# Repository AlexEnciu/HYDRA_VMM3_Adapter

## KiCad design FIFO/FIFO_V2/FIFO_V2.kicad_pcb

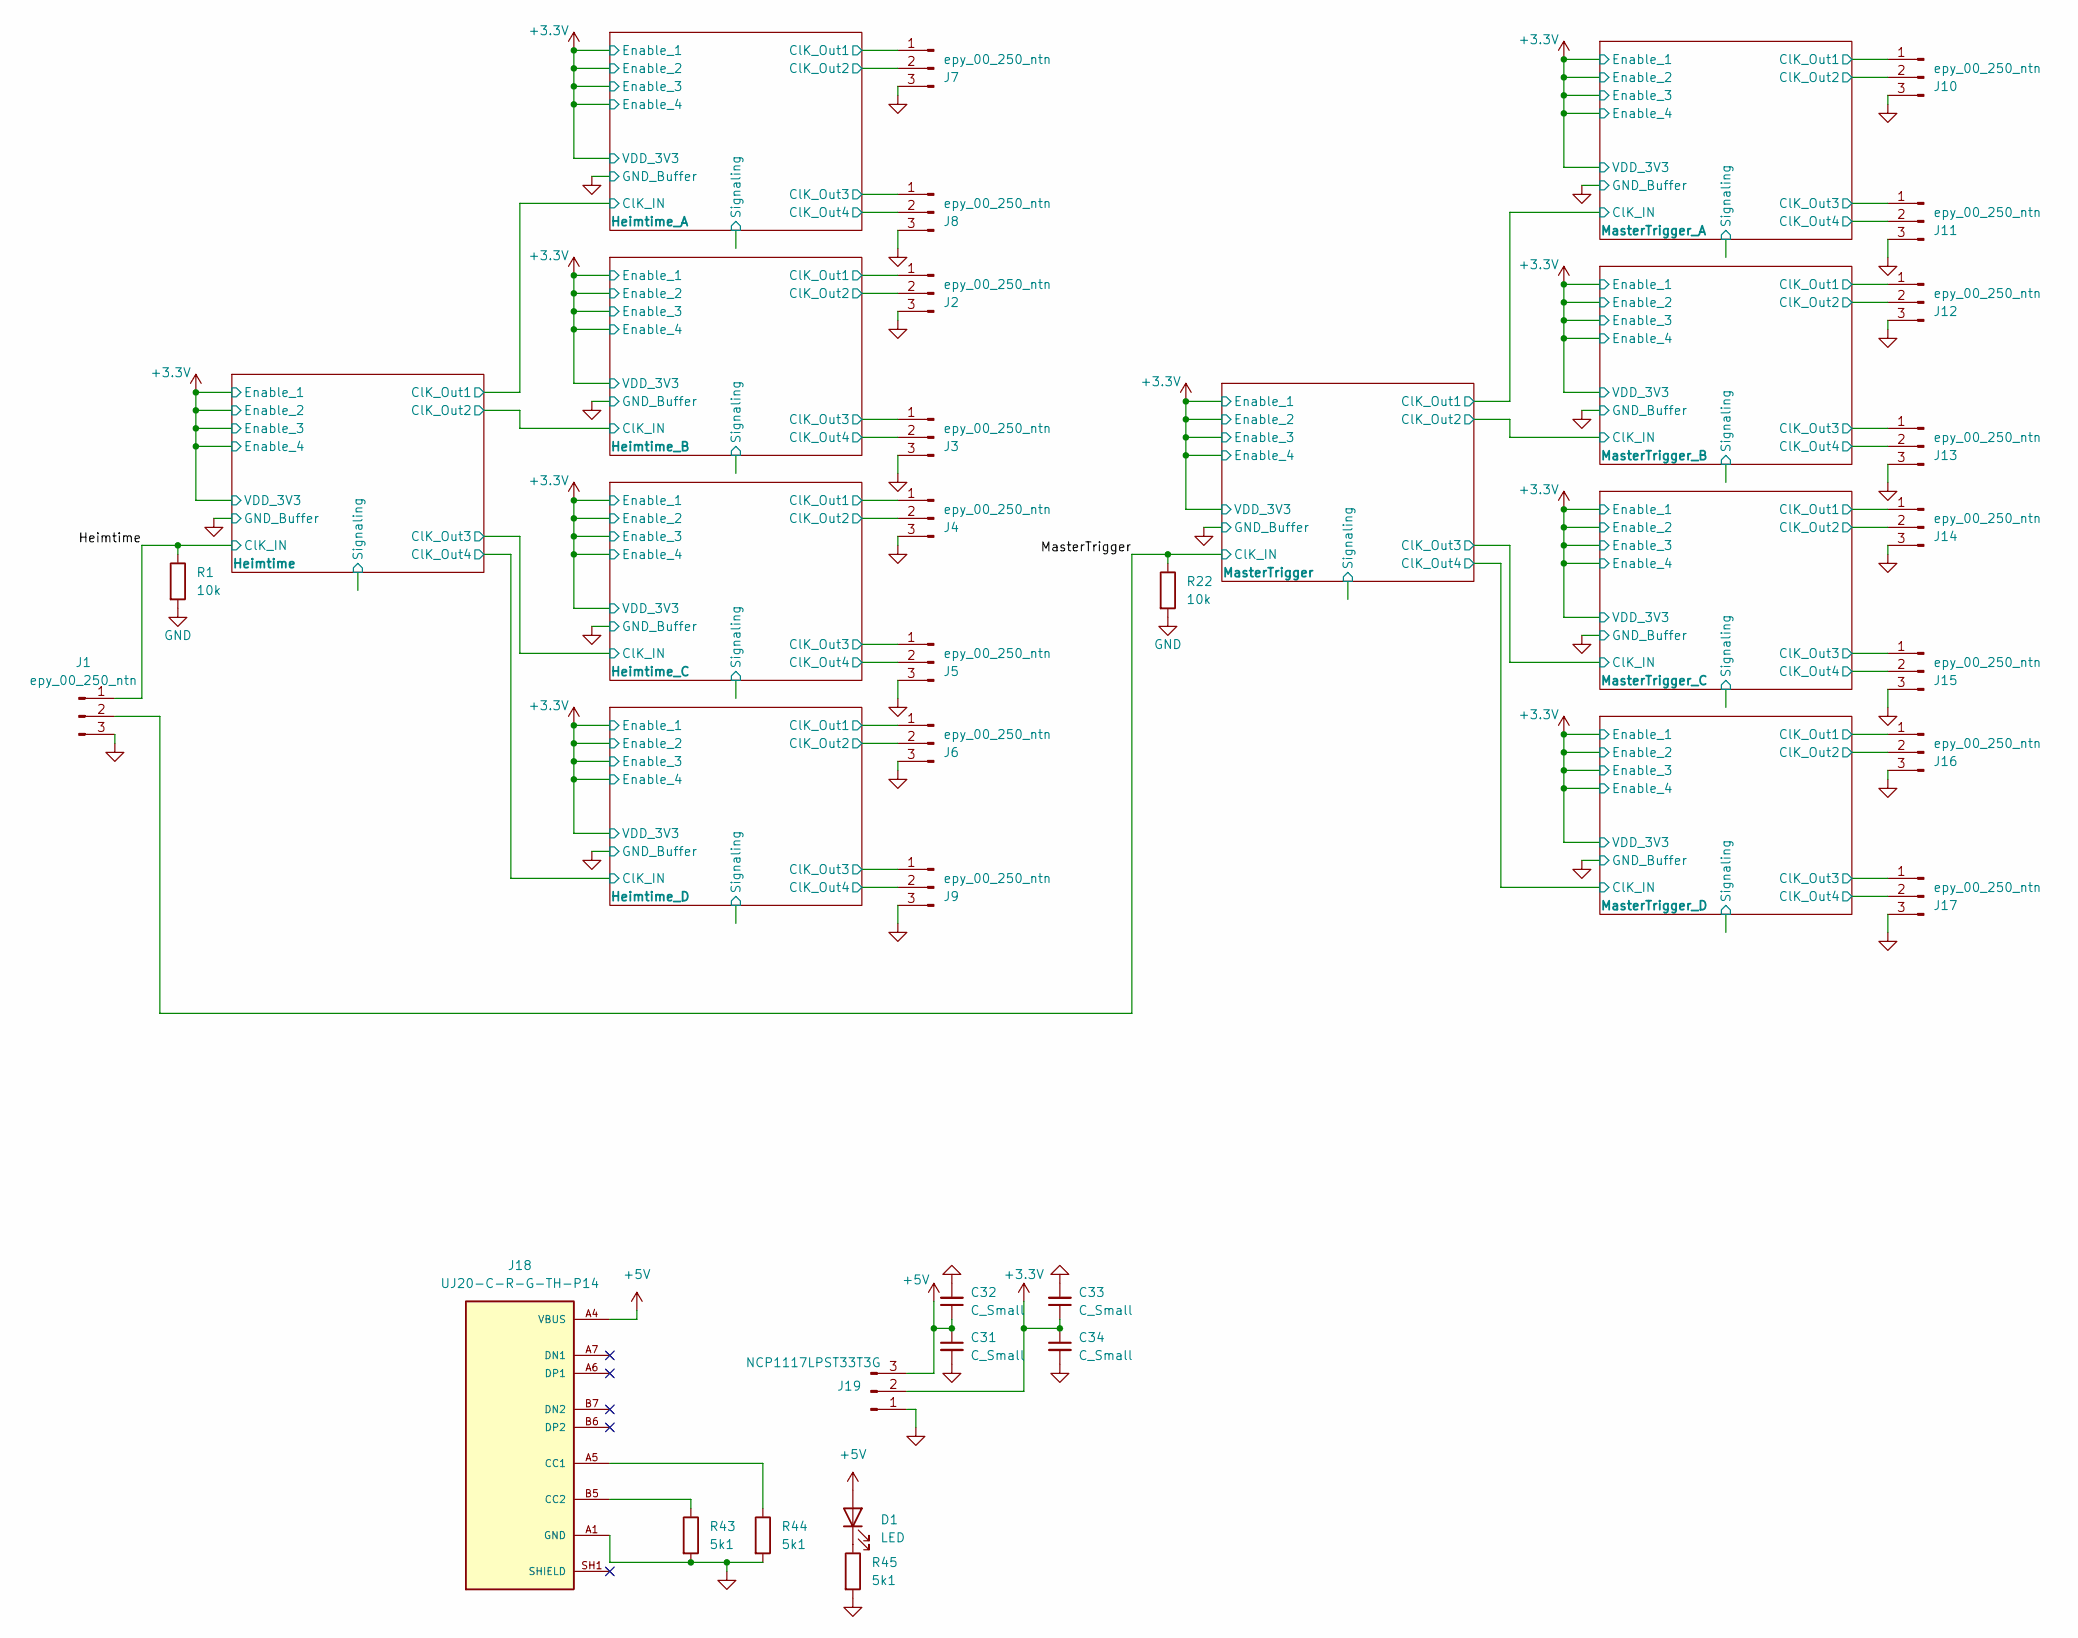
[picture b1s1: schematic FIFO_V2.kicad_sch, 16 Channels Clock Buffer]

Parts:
C31, C32, C33, C34: C_Small; C_0805_2012Metric
D1: LED; LED_D5.0mm
J1, J2, J3, J4, J5, J6, J7, J8, J9, J10, J11, J12, J13, J14, J15, J16, J17: epy_00_250_ntn; LEMO-EPY.00.250.NTN
J18: UJ20-C-R-G-TH-P14; SAMESKY_UJ20-C-R-G-TH-P14; PARTREV 1.0
J19: NCP1117LPST33T3G; SOT-223
R1, R22: 10k; R_0402_1005Metric
R43, R44, R45: 5k1; R_0402_1005Metric

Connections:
+3.3V: C33.1, C34.1, J19.2; also elsewhere on the board
+5V: C31.1, C32.1, D1.2 (A), J18.A4 (VBUS), J18.A9 (VBUS), J18.B4 (VBUS), J18.B9 (VBUS), J19.3
/Heimtime: J1.1, R1.1; also elsewhere on the board
/Heimtime_A/ClK_Out1: J7.1; also elsewhere on the board
/Heimtime_A/ClK_Out2: J7.2; also elsewhere on the board
/Heimtime_A/ClK_Out3: J8.1; also elsewhere on the board
/Heimtime_A/ClK_Out4: J8.2; also elsewhere on the board
/Heimtime_B/ClK_Out1: J2.1; also elsewhere on the board
/Heimtime_B/ClK_Out2: J2.2; also elsewhere on the board
/Heimtime_B/ClK_Out3: J3.1; also elsewhere on the board
/Heimtime_B/ClK_Out4: J3.2; also elsewhere on the board
/Heimtime_C/ClK_Out1: J4.1; also elsewhere on the board
/Heimtime_C/ClK_Out2: J4.2; also elsewhere on the board
/Heimtime_C/ClK_Out3: J5.1; also elsewhere on the board
/Heimtime_C/ClK_Out4: J5.2; also elsewhere on the board
/Heimtime_D/ClK_Out1: J6.1; also elsewhere on the board
/Heimtime_D/ClK_Out2: J6.2; also elsewhere on the board
/Heimtime_D/ClK_Out3: J9.1; also elsewhere on the board
/Heimtime_D/ClK_Out4: J9.2; also elsewhere on the board
/MasterTrigger: J1.2, R22.1; also elsewhere on the board
/MasterTrigger_A/ClK_Out1: J10.1; also elsewhere on the board
/MasterTrigger_A/ClK_Out2: J10.2; also elsewhere on the board
/MasterTrigger_A/ClK_Out3: J11.1; also elsewhere on the board
/MasterTrigger_A/ClK_Out4: J11.2; also elsewhere on the board
/MasterTrigger_B/ClK_Out1: J12.1; also elsewhere on the board
/MasterTrigger_B/ClK_Out2: J12.2; also elsewhere on the board
/MasterTrigger_B/ClK_Out3: J13.1; also elsewhere on the board
/MasterTrigger_B/ClK_Out4: J13.2; also elsewhere on the board
/MasterTrigger_C/ClK_Out1: J14.1; also elsewhere on the board
/MasterTrigger_C/ClK_Out2: J14.2; also elsewhere on the board
/MasterTrigger_C/ClK_Out3: J15.1; also elsewhere on the board
/MasterTrigger_C/ClK_Out4: J15.2; also elsewhere on the board
/MasterTrigger_D/ClK_Out1: J16.1; also elsewhere on the board
/MasterTrigger_D/ClK_Out2: J16.2; also elsewhere on the board
/MasterTrigger_D/ClK_Out3: J17.1; also elsewhere on the board
/MasterTrigger_D/ClK_Out4: J17.2; also elsewhere on the board
GND: C31.2, C32.2, C33.2, C34.2, J1.3, J2.3, J3.3, J4.3, J5.3, J6.3, J7.3, J8.3, J9.3, J10.3, J11.3, J12.3, J13.3, J14.3, J15.3, J16.3, J17.3, J18.A1 (GND), J18.A12 (GND), J18.B1 (GND), J18.B12 (GND), J19.1, R1.2, R22.2, R43.2, R44.2, R45.2; also elsewhere on the board
unnamed: D1.1 (K), R45.1
unnamed: J18.A5 (CC1), R44.1
unnamed: J18.B5 (CC2), R43.1

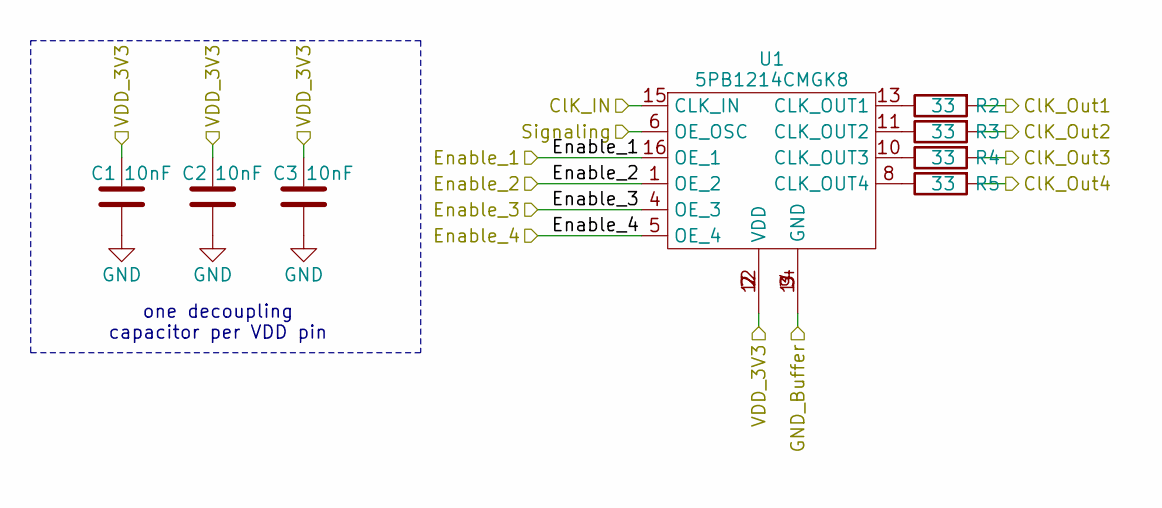
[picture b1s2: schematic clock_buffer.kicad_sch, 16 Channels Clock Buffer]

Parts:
C1, C2, C3: 10nF; C_0402_1005Metric
R2, R3, R4, R5: 33; R_0402_1005Metric
U1: 5PB1214CMGK8

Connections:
+3.3V: C1.2, C2.2, C3.2, U1.1 (OE_2), U1.2 (VDD), U1.4 (OE_3), U1.5 (OE_4), U1.7 (VDD), U1.12 (VDD), U1.16 (OE_1); also elsewhere on the board
/Heimtime: U1.15 (CLK_IN); also elsewhere on the board
/Heimtime/ClK_Out1: R2.2; also elsewhere on the board
/Heimtime/ClK_Out2: R3.2; also elsewhere on the board
/Heimtime/ClK_Out3: R4.2; also elsewhere on the board
/Heimtime/ClK_Out4: R5.2; also elsewhere on the board
/Heimtime/Signaling: U1.6 (OE_OSC)
GND: C1.1, C2.1, C3.1, U1.3 (GND), U1.9 (GND), U1.14 (GND); also elsewhere on the board
unnamed: R2.1, U1.13 (CLK_OUT1)
unnamed: R3.1, U1.11 (CLK_OUT2)
unnamed: R4.1, U1.10 (CLK_OUT3)
unnamed: R5.1, U1.8 (CLK_OUT4)

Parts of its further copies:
C4, C5, C6, C7, C8, C9, C10, C11, C12, C13, C14, C15, C16, C17, C18, C19, C20, C21, C22, C23, C24, C25, C26, C27, C28, C29, C30: 10nF; C_0402_1005Metric
R6, R7, R8, R9, R10, R11, R12, R13, R14, R15, R16, R17, R18, R19, R20, R21, R23, R24, R25, R26, R27, R28, R29, R30, R31, R32, R33, R34, R35, R36, R37, R38, R39, R40, R41, R42: 33; R_0402_1005Metric
U2, U3, U4, U5, U6, U7, U8, U9, U10: 5PB1214CMGK8

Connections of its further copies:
+3.3V: C4.2, C5.2, C6.2, C7.2, C8.2, C9.2, C10.2, C11.2, C12.2, C13.2, C14.2, C15.2, C16.2, C17.2, C18.2, C19.2, C20.2, C21.2, C22.2, C23.2, C24.2, C25.2, C26.2, C27.2, C28.2, C29.2, C30.2, U2.1 (OE_2), U2.2 (VDD), U2.4 (OE_3), U2.5 (OE_4), U2.7 (VDD), U2.12 (VDD), U2.16 (OE_1), U3.1 (OE_2), U3.2 (VDD), U3.4 (OE_3), U3.5 (OE_4), U3.7 (VDD), U3.12 (VDD), U3.16 (OE_1), U4.1 (OE_2), U4.2 (VDD), U4.4 (OE_3), U4.5 (OE_4), U4.7 (VDD), U4.12 (VDD), U4.16 (OE_1), U5.1 (OE_2), U5.2 (VDD), U5.4 (OE_3), U5.5 (OE_4), U5.7 (VDD), U5.12 (VDD), U5.16 (OE_1), U6.1 (OE_2), U6.2 (VDD), U6.4 (OE_3), U6.5 (OE_4), U6.7 (VDD), U6.12 (VDD), U6.16 (OE_1), U7.1 (OE_2), U7.2 (VDD), U7.4 (OE_3), U7.5 (OE_4), U7.7 (VDD), U7.12 (VDD), U7.16 (OE_1), U8.1 (OE_2), U8.2 (VDD), U8.4 (OE_3), U8.5 (OE_4), U8.7 (VDD), U8.12 (VDD), U8.16 (OE_1), U9.1 (OE_2), U9.2 (VDD), U9.4 (OE_3), U9.5 (OE_4), U9.7 (VDD), U9.12 (VDD), U9.16 (OE_1), U10.1 (OE_2), U10.2 (VDD), U10.4 (OE_3), U10.5 (OE_4), U10.7 (VDD), U10.12 (VDD), U10.16 (OE_1); also elsewhere on the board
/Heimtime/ClK_Out1: U2.15 (CLK_IN); also elsewhere on the board
/Heimtime/ClK_Out2: U3.15 (CLK_IN); also elsewhere on the board
/Heimtime/ClK_Out3: U4.15 (CLK_IN); also elsewhere on the board
/Heimtime/ClK_Out4: U5.15 (CLK_IN); also elsewhere on the board
/Heimtime_A/ClK_Out1: R7.2; also elsewhere on the board
/Heimtime_A/ClK_Out2: R8.2; also elsewhere on the board
/Heimtime_A/ClK_Out3: R9.2; also elsewhere on the board
/Heimtime_A/ClK_Out4: R10.2; also elsewhere on the board
/Heimtime_A/Signaling: U2.6 (OE_OSC)
/Heimtime_B/ClK_Out1: R6.2; also elsewhere on the board
/Heimtime_B/ClK_Out2: R11.2; also elsewhere on the board
/Heimtime_B/ClK_Out3: R12.2; also elsewhere on the board
/Heimtime_B/ClK_Out4: R13.2; also elsewhere on the board
/Heimtime_B/Signaling: U3.6 (OE_OSC)
/Heimtime_C/ClK_Out1: R14.2; also elsewhere on the board
/Heimtime_C/ClK_Out2: R15.2; also elsewhere on the board
/Heimtime_C/ClK_Out3: R16.2; also elsewhere on the board
/Heimtime_C/ClK_Out4: R17.2; also elsewhere on the board
/Heimtime_C/Signaling: U4.6 (OE_OSC)
/Heimtime_D/ClK_Out1: R18.2; also elsewhere on the board
/Heimtime_D/ClK_Out2: R19.2; also elsewhere on the board
/Heimtime_D/ClK_Out3: R20.2; also elsewhere on the board
/Heimtime_D/ClK_Out4: R21.2; also elsewhere on the board
/Heimtime_D/Signaling: U5.6 (OE_OSC)
/MasterTrigger: U7.15 (CLK_IN); also elsewhere on the board
/MasterTrigger/ClK_Out1: R27.2, U6.15 (CLK_IN)
/MasterTrigger/ClK_Out2: R28.2, U8.15 (CLK_IN)
/MasterTrigger/ClK_Out3: R29.2, U9.15 (CLK_IN)
/MasterTrigger/ClK_Out4: R30.2, U10.15 (CLK_IN)
/MasterTrigger/Signaling: U7.6 (OE_OSC)
/MasterTrigger_A/ClK_Out1: R23.2; also elsewhere on the board
/MasterTrigger_A/ClK_Out2: R24.2; also elsewhere on the board
/MasterTrigger_A/ClK_Out3: R25.2; also elsewhere on the board
/MasterTrigger_A/ClK_Out4: R26.2; also elsewhere on the board
/MasterTrigger_A/Signaling: U6.6 (OE_OSC)
/MasterTrigger_B/ClK_Out1: R31.2; also elsewhere on the board
/MasterTrigger_B/ClK_Out2: R32.2; also elsewhere on the board
/MasterTrigger_B/ClK_Out3: R33.2; also elsewhere on the board
/MasterTrigger_B/ClK_Out4: R34.2; also elsewhere on the board
/MasterTrigger_B/Signaling: U8.6 (OE_OSC)
/MasterTrigger_C/ClK_Out1: R35.2; also elsewhere on the board
/MasterTrigger_C/ClK_Out2: R36.2; also elsewhere on the board
/MasterTrigger_C/ClK_Out3: R37.2; also elsewhere on the board
/MasterTrigger_C/ClK_Out4: R38.2; also elsewhere on the board
/MasterTrigger_C/Signaling: U9.6 (OE_OSC)
/MasterTrigger_D/ClK_Out1: R39.2; also elsewhere on the board
/MasterTrigger_D/ClK_Out2: R40.2; also elsewhere on the board
/MasterTrigger_D/ClK_Out3: R41.2; also elsewhere on the board
/MasterTrigger_D/ClK_Out4: R42.2; also elsewhere on the board
/MasterTrigger_D/Signaling: U10.6 (OE_OSC)
GND: C4.1, C5.1, C6.1, C7.1, C8.1, C9.1, C10.1, C11.1, C12.1, C13.1, C14.1, C15.1, C16.1, C17.1, C18.1, C19.1, C20.1, C21.1, C22.1, C23.1, C24.1, C25.1, C26.1, C27.1, C28.1, C29.1, C30.1, U2.3 (GND), U2.9 (GND), U2.14 (GND), U3.3 (GND), U3.9 (GND), U3.14 (GND), U4.3 (GND), U4.9 (GND), U4.14 (GND), U5.3 (GND), U5.9 (GND), U5.14 (GND), U6.3 (GND), U6.9 (GND), U6.14 (GND), U7.3 (GND), U7.9 (GND), U7.14 (GND), U8.3 (GND), U8.9 (GND), U8.14 (GND), U9.3 (GND), U9.9 (GND), U9.14 (GND), U10.3 (GND), U10.9 (GND), U10.14 (GND); also elsewhere on the board
unnamed: R7.1, U2.13 (CLK_OUT1)
unnamed: R8.1, U2.11 (CLK_OUT2)
unnamed: R9.1, U2.10 (CLK_OUT3)
unnamed: R10.1, U2.8 (CLK_OUT4)
unnamed: R6.1, U3.13 (CLK_OUT1)
unnamed: R11.1, U3.11 (CLK_OUT2)
unnamed: R12.1, U3.10 (CLK_OUT3)
unnamed: R13.1, U3.8 (CLK_OUT4)
unnamed: R14.1, U4.13 (CLK_OUT1)
unnamed: R15.1, U4.11 (CLK_OUT2)
unnamed: R16.1, U4.10 (CLK_OUT3)
unnamed: R17.1, U4.8 (CLK_OUT4)
unnamed: R18.1, U5.13 (CLK_OUT1)
unnamed: R19.1, U5.11 (CLK_OUT2)
unnamed: R20.1, U5.10 (CLK_OUT3)
unnamed: R21.1, U5.8 (CLK_OUT4)
unnamed: R23.1, U6.13 (CLK_OUT1)
unnamed: R24.1, U6.11 (CLK_OUT2)
unnamed: R25.1, U6.10 (CLK_OUT3)
unnamed: R26.1, U6.8 (CLK_OUT4)
unnamed: R27.1, U7.13 (CLK_OUT1)
unnamed: R28.1, U7.11 (CLK_OUT2)
unnamed: R29.1, U7.10 (CLK_OUT3)
unnamed: R30.1, U7.8 (CLK_OUT4)
unnamed: R31.1, U8.13 (CLK_OUT1)
unnamed: R32.1, U8.11 (CLK_OUT2)
unnamed: R33.1, U8.10 (CLK_OUT3)
unnamed: R34.1, U8.8 (CLK_OUT4)
unnamed: R35.1, U9.13 (CLK_OUT1)
unnamed: R36.1, U9.11 (CLK_OUT2)
unnamed: R37.1, U9.10 (CLK_OUT3)
unnamed: R38.1, U9.8 (CLK_OUT4)
unnamed: R39.1, U10.13 (CLK_OUT1)
unnamed: R40.1, U10.11 (CLK_OUT2)
unnamed: R41.1, U10.10 (CLK_OUT3)
unnamed: R42.1, U10.8 (CLK_OUT4)

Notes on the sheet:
one decoupling capacitor per VDD pin

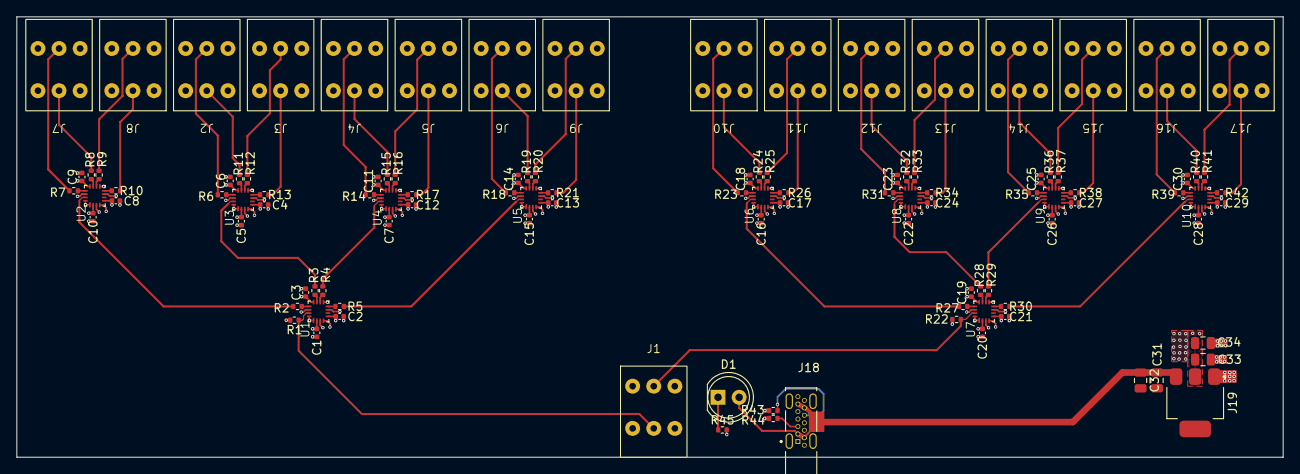
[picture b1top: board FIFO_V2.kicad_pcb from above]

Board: 4 copper layers, 152.4 x 53.0 mm, 109 parts (0 on the bottom side), 88 nets.

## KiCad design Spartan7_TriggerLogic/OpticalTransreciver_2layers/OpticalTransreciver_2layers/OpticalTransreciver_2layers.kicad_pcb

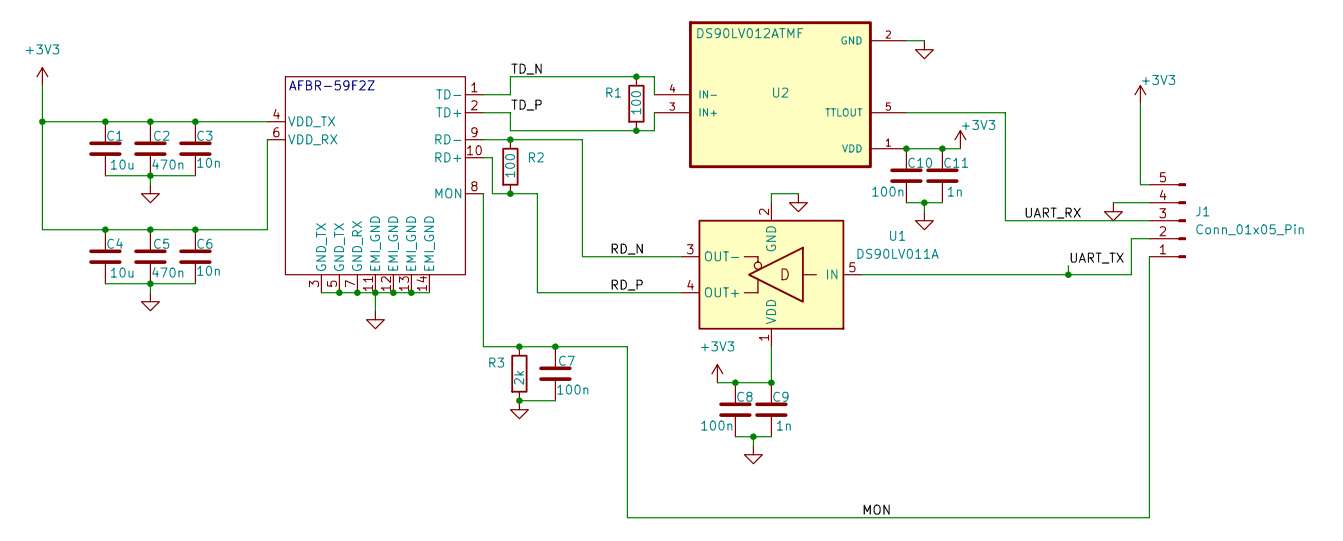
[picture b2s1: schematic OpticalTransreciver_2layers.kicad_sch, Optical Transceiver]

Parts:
C1, C4: 10u; C_0603_1608Metric
C2, C5: 470n; C_0603_1608Metric
C3, C6: 10n; C_0603_1608Metric
C7, C8, C10: 100n; C_0603_1608Metric
C9, C11: 1n; C_0603_1608Metric
Conn1: AFBR-59F2Z; AFBR-5803ZTZ_AVA
J1: Conn_01x05_Pin; PinHeader_1x05_P2.54mm_Vertical
R1, R2: 100; R_0603_1608Metric
R3: 2k; R_0603_1608Metric
U1: DS90LV011A; SOT-23-5
U2: DS90LV012ATMF; SOT-23-5

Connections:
+3V3: C1.1, C2.1, C3.1, C4.1, C5.1, C6.1, C8.1, C9.1, C10.1, C11.1, Conn1.4 (VDD_TX), Conn1.6 (VDD_RX), J1.5, U1.1 (VDD), U2.1 (VDD)
/MON: C7.1, Conn1.8 (MON), J1.1, R3.1
/RD_N: Conn1.9 (RD-), R2.1, U1.3 (OUT-)
/RD_P: Conn1.10 (RD+), R2.2, U1.4 (OUT+)
/TD_N: Conn1.1 (TD-), R1.1, U2.4 (IN-)
/TD_P: Conn1.2 (TD+), R1.2, U2.3 (IN+)
/UART_RX: J1.3, U2.5 (TTLOUT)
/UART_TX: J1.2, U1.5 (IN)
GND: C1.2, C2.2, C3.2, C4.2, C5.2, C6.2, C7.2, C8.2, C9.2, C10.2, C11.2, Conn1.3 (GND_TX), Conn1.5 (GND_TX), Conn1.7 (GND_RX), Conn1.11 (EMI_GND), Conn1.12 (EMI_GND), Conn1.13 (EMI_GND), Conn1.14 (EMI_GND), J1.4, R3.2, U1.2 (GND), U2.2 (GND)

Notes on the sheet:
AFBR-59F2Z

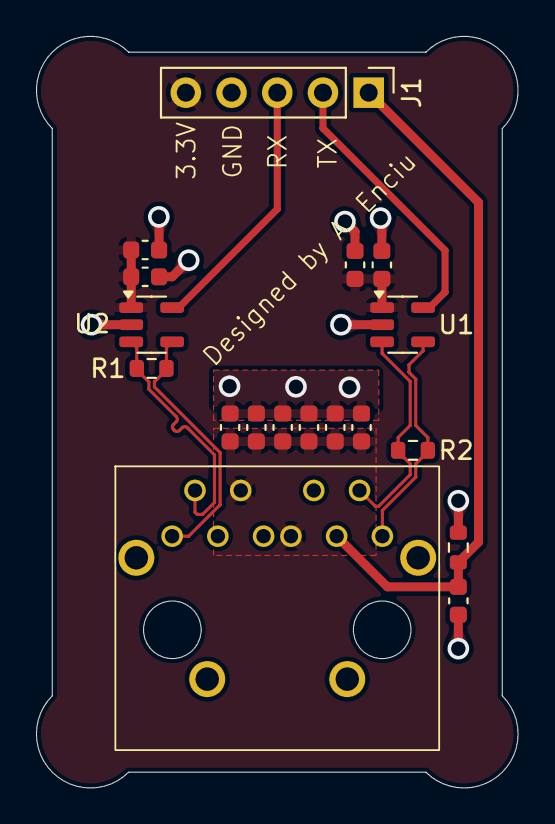
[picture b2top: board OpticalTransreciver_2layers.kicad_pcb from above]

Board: 2 copper layers, 26.8 x 41.8 mm, 18 parts (0 on the bottom side), 9 nets.

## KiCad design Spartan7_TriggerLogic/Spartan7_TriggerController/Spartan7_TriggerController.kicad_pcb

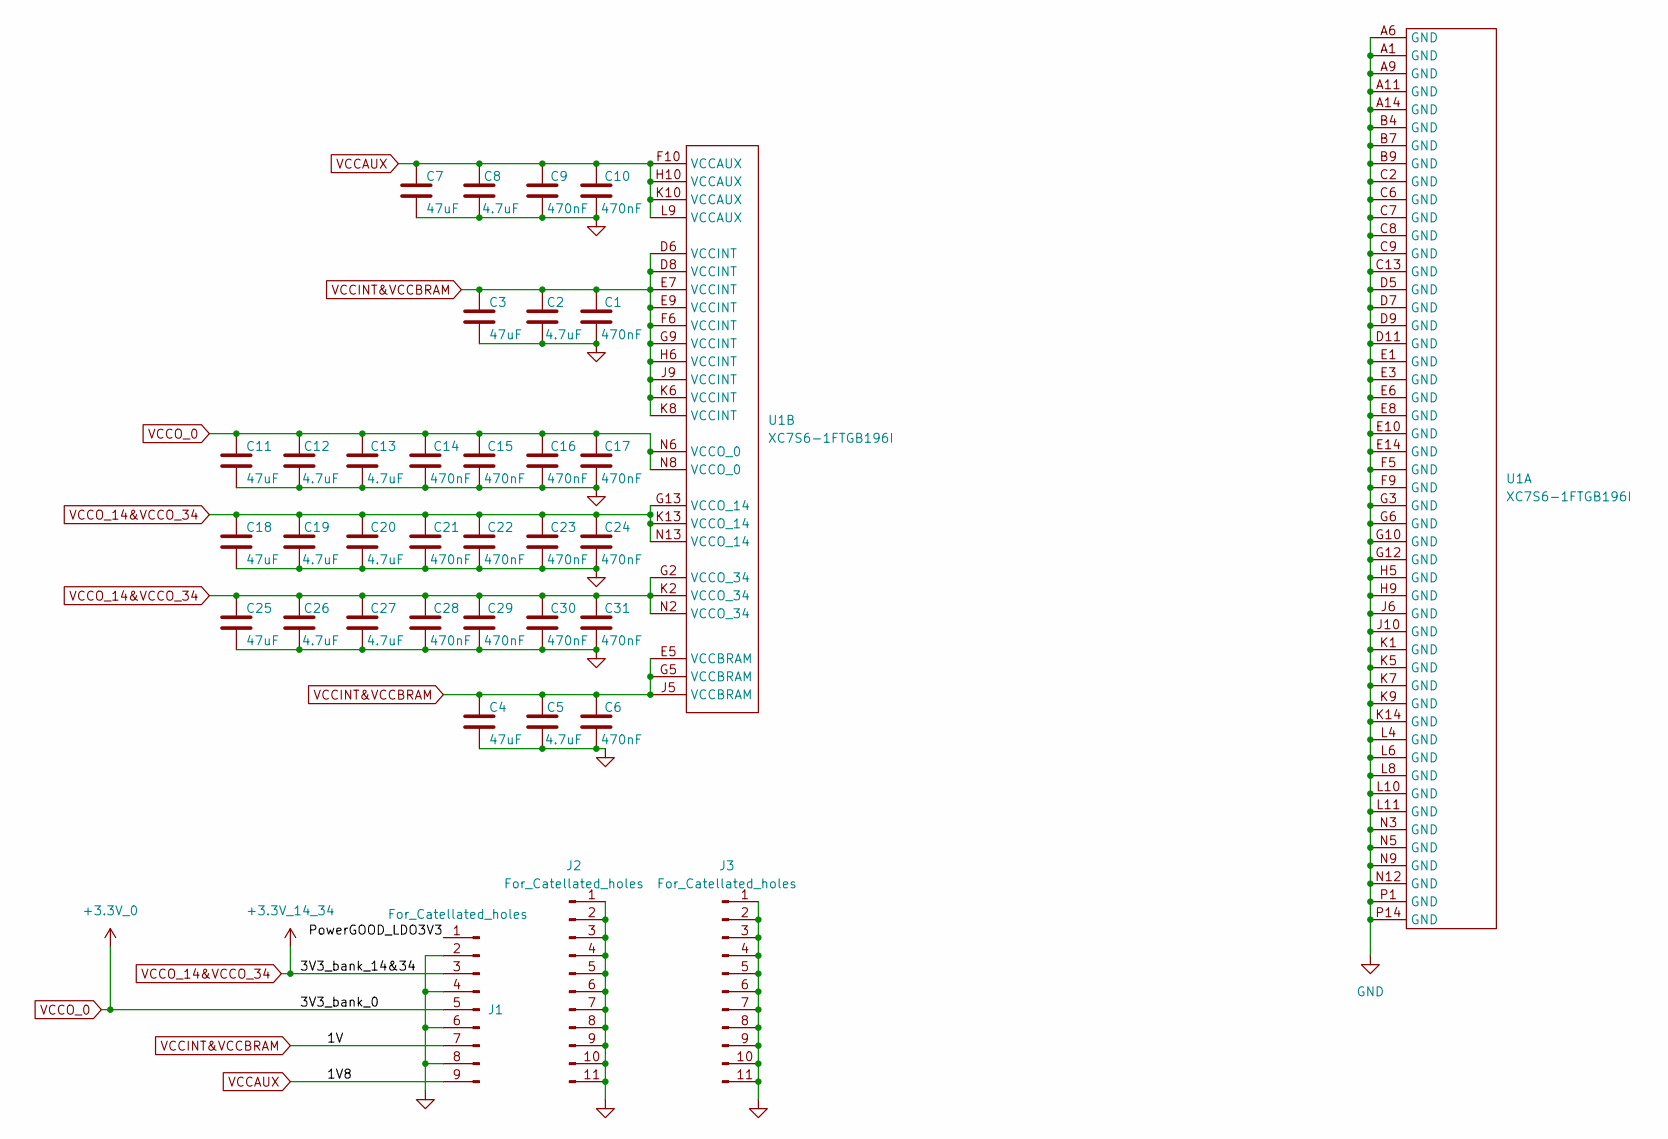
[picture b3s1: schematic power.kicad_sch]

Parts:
C1, C6, C9, C10, C14, C15, C16, C17, C21, C22, C23, C24, C28, C29, C30, C31: 470nF; C_0402_1005Metric
C2, C5, C8, C12, C13, C19, C20, C26, C27: 4.7uF; C_0603_1608Metric
C3, C4, C7, C11, C18, C25: 47uF; C_1210_3225Metric
J1: For_Catellated_holes; PinHeader_1x09_P2.54mm_Vertical
J2, J3: For_Catellated_holes; PinHeader_1x11_P2.54mm_Vertical
U1: XC7S6-1FTGB196I; BGA196C100P14X14_1500X1500X155N

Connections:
/Power/PowerGOOD_LDO3V3: J1.1
GND: C1.2, C2.2, C3.2, C4.2, C5.2, C6.2, C7.2, C8.2, C9.2, C10.2, C11.2, C12.2, C13.2, C14.2, C15.2, C16.2, C17.2, C18.2, C19.2, C20.2, C21.2, C22.2, C23.2, C24.2, C25.2, C26.2, C27.2, C28.2, C29.2, C30.2, C31.2, J1.2, J1.4, J1.6, J1.8, J2.1, J2.2, J2.3, J2.4, J2.5, J2.6, J2.7, J2.8, J2.9, J2.10, J2.11, J3.1, J3.2, J3.3, J3.4, J3.5, J3.6, J3.7, J3.8, J3.9, J3.10, J3.11, U1.A1 (GND), U1.A6 (GND), U1.A9 (GND), U1.A11 (GND), U1.A14 (GND), U1.B4 (GND), U1.B7 (GND), U1.B9 (GND), U1.C2 (GND), U1.C6 (GND), U1.C7 (GND), U1.C8 (GND), U1.C9 (GND), U1.C13 (GND), U1.D5 (GND), U1.D7 (GND), U1.D9 (GND), U1.D11 (GND), U1.E1 (GND), U1.E3 (GND), U1.E6 (GND), U1.E8 (GND), U1.E10 (GND), U1.E14 (GND), U1.F5 (GND), U1.F9 (GND), U1.G3 (GND), U1.G6 (GND), U1.G10 (GND), U1.G12 (GND), U1.H5 (GND), U1.H9 (GND), U1.J6 (GND), U1.J10 (GND), U1.K1 (GND), U1.K5 (GND), U1.K7 (GND), U1.K9 (GND), U1.K14 (GND), U1.L4 (GND), U1.L6 (GND), U1.L8 (GND), U1.L10 (GND), U1.L11 (GND), U1.N3 (GND), U1.N5 (GND), U1.N9 (GND), U1.N12 (GND), U1.P1 (GND), U1.P14 (GND); also elsewhere on the board
VCCAUX: C7.1, C8.1, C9.1, C10.1, J1.9, U1.F10 (VCCAUX), U1.H10 (VCCAUX), U1.K10 (VCCAUX), U1.L9 (VCCAUX)
VCCINT&VCCBRAM: C1.1, C2.1, C3.1, C4.1, C5.1, C6.1, J1.7, U1.D6 (VCCINT), U1.D8 (VCCINT), U1.E5 (VCCBRAM), U1.E7 (VCCINT), U1.E9 (VCCINT), U1.F6 (VCCINT), U1.G5 (VCCBRAM), U1.G9 (VCCINT), U1.H6 (VCCINT), U1.J5 (VCCBRAM), U1.J9 (VCCINT), U1.K6 (VCCINT), U1.K8 (VCCINT)
VCCO_0: C11.1, C12.1, C13.1, C14.1, C15.1, C16.1, C17.1, J1.5, U1.N6 (VCCO_0), U1.N8 (VCCO_0)
VCCO_14&VCCO_34: C18.1, C19.1, C20.1, C21.1, C22.1, C23.1, C24.1, C25.1, C26.1, C27.1, C28.1, C29.1, C30.1, C31.1, J1.3, U1.G2 (VCCO_34), U1.G13 (VCCO_14), U1.K2 (VCCO_34), U1.K13 (VCCO_14), U1.N2 (VCCO_34), U1.N13 (VCCO_14); also elsewhere on the board

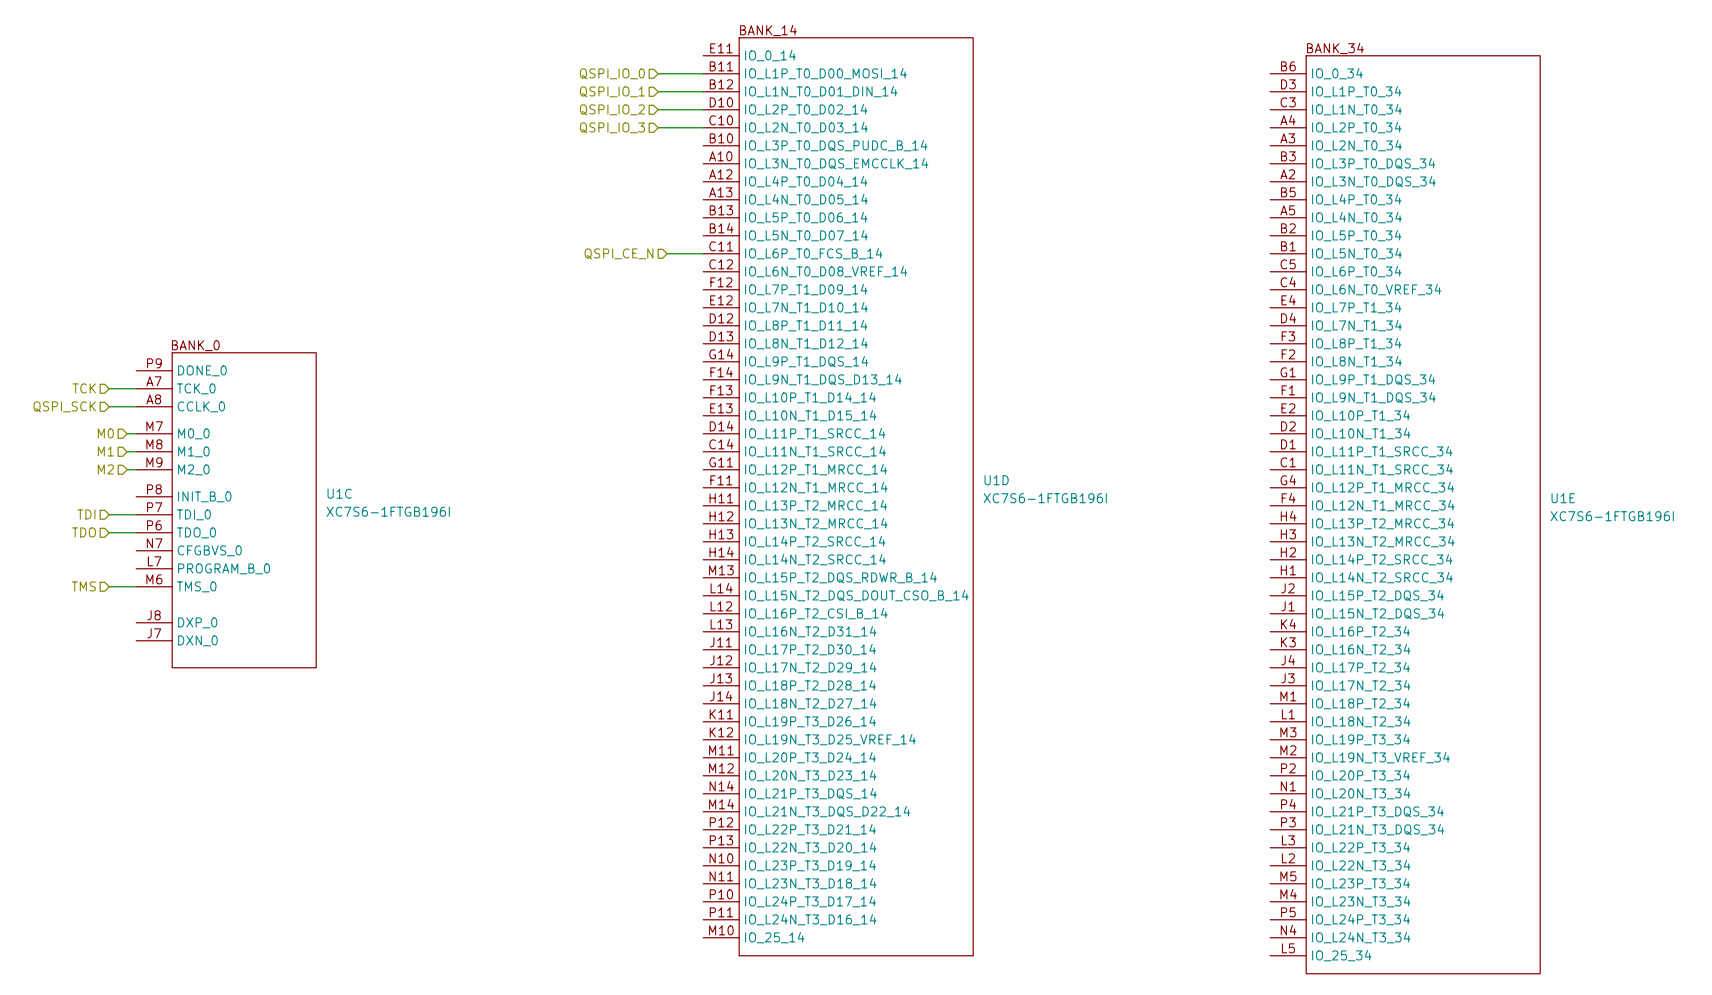
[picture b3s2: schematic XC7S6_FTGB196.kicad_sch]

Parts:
U1: XC7S6-1FTGB196I; BGA196C100P14X14_1500X1500X155N

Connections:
/Boot_Mode/M0: U1.M7 (M0_0); also elsewhere on the board
/Boot_Mode/M1: U1.M8 (M1_0); also elsewhere on the board
/Boot_Mode/M2: U1.M9 (M2_0); also elsewhere on the board
/JTAG/TCK: U1.A7 (TCK_0); also elsewhere on the board
/JTAG/TDI: U1.P7 (TDI_0); also elsewhere on the board
/JTAG/TDO: U1.P6 (TDO_0); also elsewhere on the board
/JTAG/TMS: U1.M6 (TMS_0); also elsewhere on the board
/QSPI/QSPI_CE_N: U1.C11 (IO_L6P_T0_FCS_B_14); also elsewhere on the board
/QSPI/QSPI_IO_0: U1.B11 (IO_L1P_T0_D00_MOSI_14); also elsewhere on the board
/QSPI/QSPI_IO_1: U1.B12 (IO_L1N_T0_D01_DIN_14); also elsewhere on the board
/QSPI/QSPI_IO_2: U1.D10 (IO_L2P_T0_D02_14); also elsewhere on the board
/QSPI/QSPI_IO_3: U1.C10 (IO_L2N_T0_D03_14); also elsewhere on the board
/QSPI/QSPI_SCK: U1.A8 (CCLK_0); also elsewhere on the board

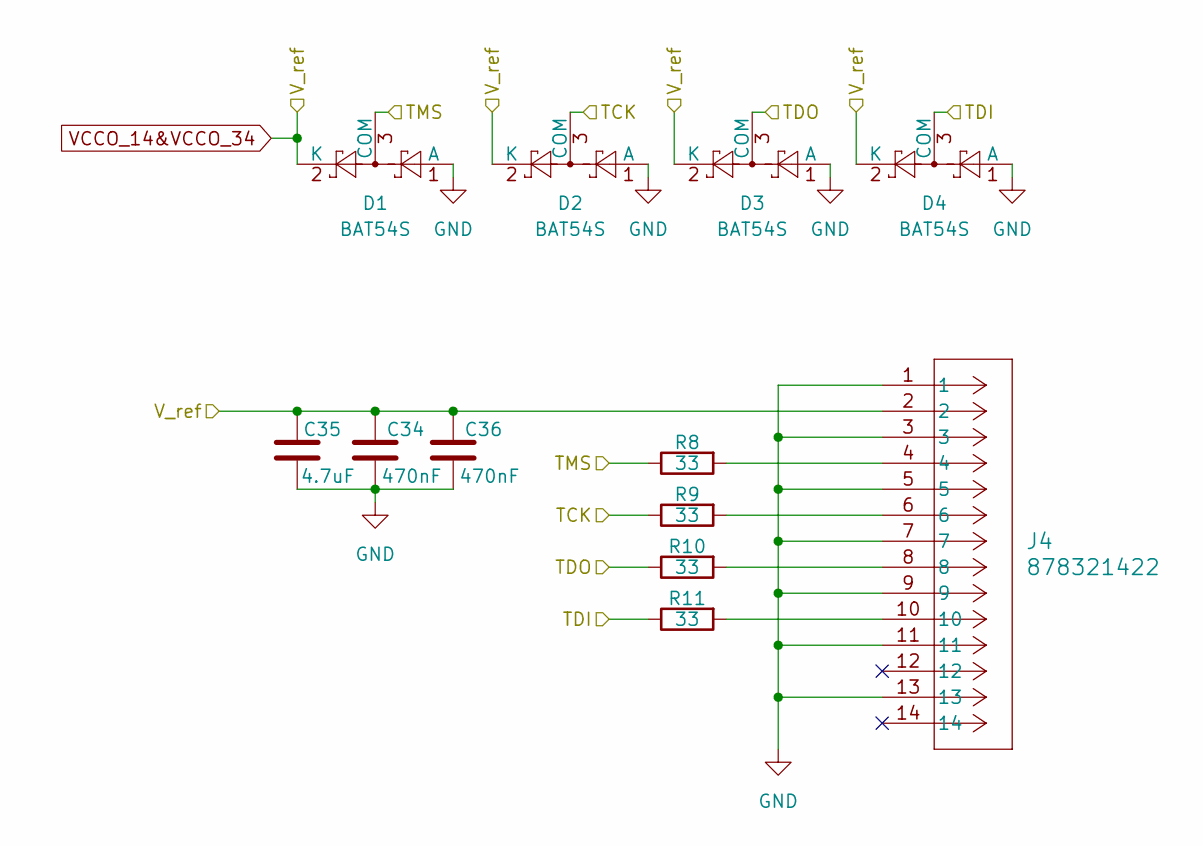
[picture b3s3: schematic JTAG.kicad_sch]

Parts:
C34, C36: 470nF; C_0402_1005Metric
C35: 4.7uF; C_0603_1608Metric
D1, D2, D3, D4: BAT54S; SOT-23
J4: 878321422; CONN14_878321422_MOL
R8, R9, R10, R11: 33; R_0402_1005Metric

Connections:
/JTAG/TCK: D2.3 (COM), R9.1; also elsewhere on the board
/JTAG/TDI: D4.3 (COM), R11.1; also elsewhere on the board
/JTAG/TDO: D3.3 (COM), R10.1; also elsewhere on the board
/JTAG/TMS: D1.3 (COM), R8.1; also elsewhere on the board
GND: C34.2, C35.2, C36.2, D1.1 (A), D2.1 (A), D3.1 (A), D4.1 (A), J4.1, J4.3, J4.5, J4.7, J4.9, J4.11, J4.13; also elsewhere on the board
unnamed: J4.4, R8.2
unnamed: J4.6, R9.2
unnamed: J4.8, R10.2
unnamed: J4.10, R11.2
VCCO_14&VCCO_34: C34.1, C35.1, C36.1, D1.2 (K), D2.2 (K), D3.2 (K), D4.2 (K), J4.2; also elsewhere on the board

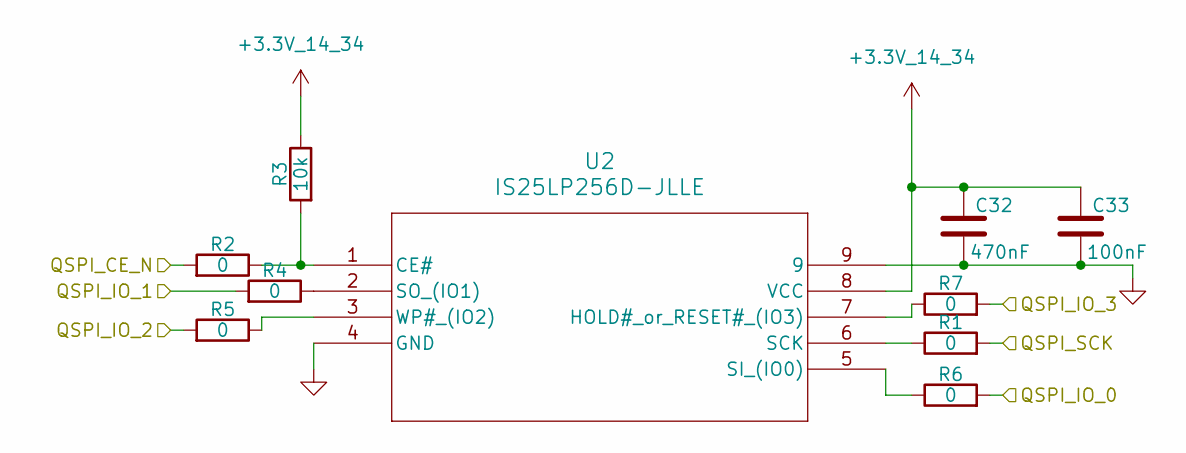
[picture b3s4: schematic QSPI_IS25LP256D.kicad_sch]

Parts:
C32: 470nF; C_0402_1005Metric
C33: 100nF; C_0402_1005Metric
R1, R2, R4, R5, R6, R7: 0; R_0402_1005Metric
R3: 10k; R_0402_1005Metric
U2: IS25LP256D-JLLE; WSON_6D-JLLE_ISI

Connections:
/QSPI/QSPI_CE_N: R2.2; also elsewhere on the board
/QSPI/QSPI_IO_0: R6.2; also elsewhere on the board
/QSPI/QSPI_IO_1: R4.2; also elsewhere on the board
/QSPI/QSPI_IO_2: R5.2; also elsewhere on the board
/QSPI/QSPI_IO_3: R7.2; also elsewhere on the board
/QSPI/QSPI_SCK: R1.2; also elsewhere on the board
GND: C32.2, C33.2, U2.4 (GND), U2.9; also elsewhere on the board
unnamed: R2.1, R3.2, U2.1 (CE#)
unnamed: R7.1, U2.7 (HOLD#_or_RESET#_(IO3))
unnamed: R1.1, U2.6 (SCK)
unnamed: R6.1, U2.5 (SI_(IO0))
unnamed: R4.1, U2.2 (SO_(IO1))
unnamed: R5.1, U2.3 (WP#_(IO2))
VCCO_14&VCCO_34: C32.1, C33.1, R3.1, U2.8 (VCC); also elsewhere on the board

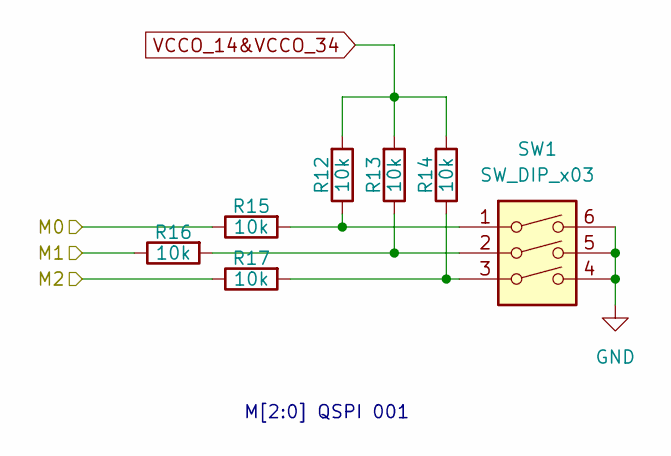
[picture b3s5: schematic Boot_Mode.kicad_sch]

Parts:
R12, R13, R14, R15, R16, R17: 10k; R_0402_1005Metric
SW1: SW_DIP_x03; SW_DIP_SPSTx03_Slide_6.7x9.18mm_W6.73mm_P2.54mm_LowProfile_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

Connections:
/Boot_Mode/M0: R15.1; also elsewhere on the board
/Boot_Mode/M1: R16.1; also elsewhere on the board
/Boot_Mode/M2: R17.1; also elsewhere on the board
GND: SW1.4, SW1.5, SW1.6; also elsewhere on the board
unnamed: R12.1, R15.2, SW1.1
unnamed: R13.1, R16.2, SW1.2
unnamed: R14.1, R17.2, SW1.3
VCCO_14&VCCO_34: R12.2, R13.2, R14.2; also elsewhere on the board

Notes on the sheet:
M[2:0] QSPI 001
